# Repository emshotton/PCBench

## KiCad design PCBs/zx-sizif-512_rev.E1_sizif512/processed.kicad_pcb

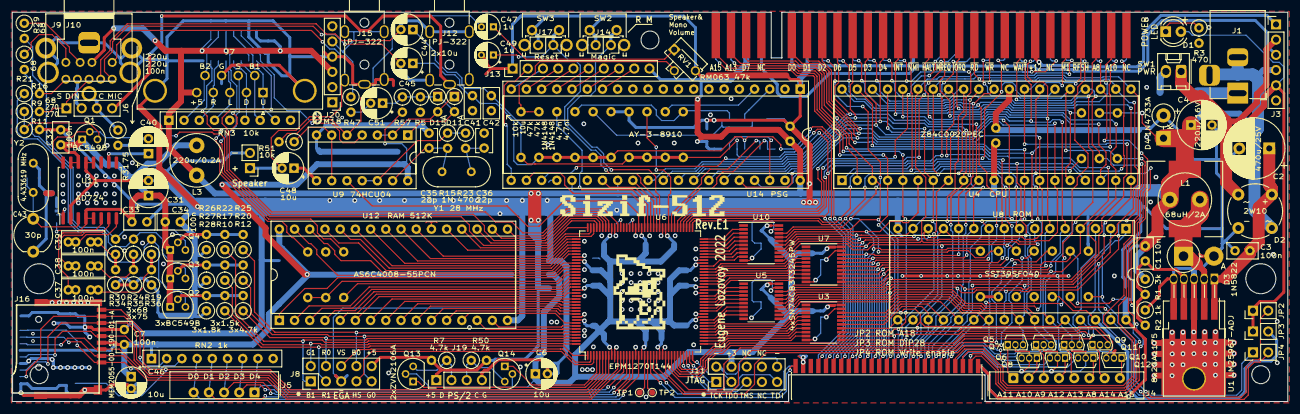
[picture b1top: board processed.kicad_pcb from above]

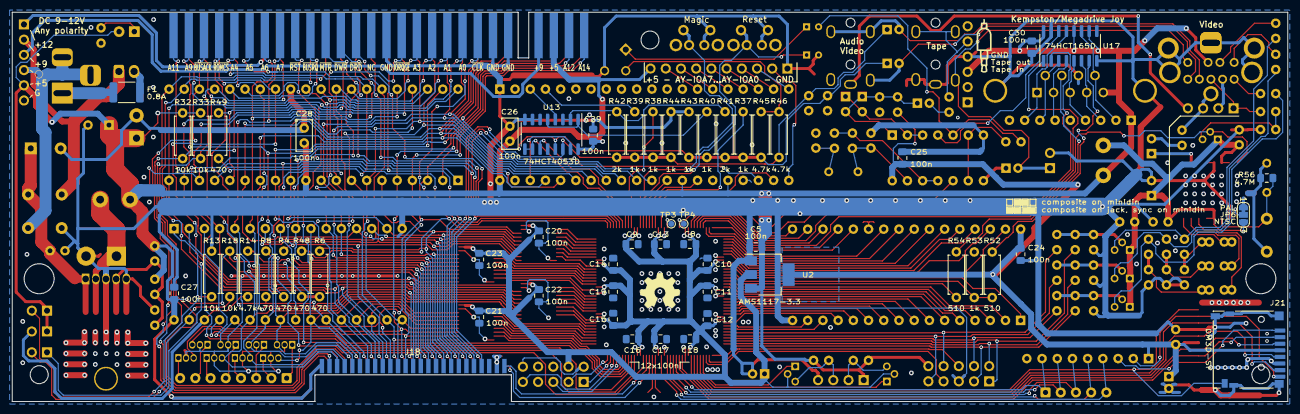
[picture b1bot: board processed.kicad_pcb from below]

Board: 2 copper layers, 213.0 x 65.0 mm, 193 parts (58 on the bottom side), 248 nets.

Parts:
C1: 10n; C_Disc_D5.0mm_W2.5mm_P2.50mm
C2: 470u/25V; CP_Radial_D10.0mm_P5.00mm
C3, C7, C26, C28, C32, C33, C34: 100n; C_Disc_D5.0mm_W2.5mm_P2.50mm
C4: 220u/16V; CP_Radial_D8.0mm_P3.50mm
C5, C8, C9, C10, C11, C12, C13, C14, C15, C16, C17, C18, C19, C20, C21, C22, C23, C24, C27, C29: 100n; C_0805_2012Metric_Pad1.15x1.40mm_HandSolder
C6, C44, C45, C46, C48, C51: 10u; CP_Radial_D5.0mm_P2.00mm
C25, C30: 100n; C_0805_2012Metric_Pad1.18x1.45mm_HandSolder
C31, C40: 220u; CP_Radial_D6.3mm_P2.50mm
C35, C36: 22p; C_Disc_D3.8mm_W2.6mm_P2.50mm
C37, C38, C39: 100n; C_Rect_L7.0mm_W3.5mm_P2.50mm_P5.00mm
C41, C42: 4.7n; C_Disc_D5.0mm_W2.5mm_P2.50mm
C43: 30p; C_Trim_D6.3mm_P5.50mm
C47, C49: 1u; CP_Radial_D4.0mm_P2.00mm
D1: LED; LED_D4.0mm
D2: 2W10; Diode_Bridge_Round_D10.0mm
D3: 1N5822; D_DO-201AD_P5.08mm_Vertical_AnodeUp
D4: 1N4733A; D_DO-15_P3.81mm_Vertical_KathodeUp
D11, D15: 1N4148; D_DO-35_SOD27_P2.54mm_Vertical_AnodeUp
F1: 0.8A; Fuse_1812_4532Metric_Pad1.30x3.40mm_HandSolder
H1, H2: MountingHole; MountingHole_5mm_7mm_fence
H3, H4, H5: MountingHole; MountingHole_3mm
J1: DS-210; BarrelJack_Horizontal
J2: Conn_02x28_Row_Letter_First; ZX_EDGE
J3, J20: Pin header 1x6 Pitch=2.54mm; PinHeader_1x06_P2.54mm_Vertical
J4: DS1020-08; FFC_FPC_1x08
J5: DS1020-05; FFC_FPC_1x05
J6, J19: Pin header 1x4 Pitch=2.54mm; PinHeader_1x04_P2.54mm_Vertical
J7: DB9-M; DSUB-9_Male_Horizontal_P2.77x2.84mm_EdgePinOffset4.94mm_Hou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
J8, J11: Pin header 2x5 Pitch=2.54mm; PinHeader_2x05_P2.54mm_Vertical
J9: Mini-DIN-9; minidin-9
J10: RCJ-014; CUI_RCJ-01X-WIDE
J12, J15: PJ-322
J13: Pin header 1x10 Pitch=2.54mm; PinHeader_1x10_P2.54mm_Vertical
J14, J17: Pin header 1x2 Pitch=2.54mm; PinHeader_2x01_P2.54mm_Vertical
J16: MEM2055-00-190-01-A; GCT-MEM2055-00-190-01-A
J18: Pin socket 3x25 or 2xPin socket 1x25 Pitch=1.27mm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; PinHeader_2x25_P1.27mm_Edge_SMD
J21: DM3D-SF; microSD_HC_Hirose_DM3D-SF
JP2, JP3, JP4: Jumper / Pin header 1x2 Pitch=2.54mm; PinHeader_1x02_P2.54mm_Vertical
JP6: Jumper_3_Bridged12; SolderJumper-3_P1.3mm_Bridged12_RoundedPad1.0x1.5mm_NumberL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
L1: 68uH/2A; L_Radial_D8.7mm_P5.00mm_Fastron_07HCP
L2: 68uH/2A; L_12x12mm_H8mm
L3: 220u/0.2A; L_Radial_D8.7mm_P5.00mm_Fastron_07HCP
LOGO1: graphic; black-mage-12.5x8.6-r
LOGO2: Logo_Open_Hardware_Small; OSHW-Symbol_6.7x6mm_SilkScreen
LOGO3: graphic; jack35
LOGO4: graphic; bluetooth_small
LOGO5: graphic; sizif512
LS1: Pin header 1x2 Pitch=2.54mm; PinHeader_1x02_P2.54mm_Vertical
Q1, Q2, Q3, Q4: BC549B; TO-92
Q5, Q6, Q7, Q8, Q9, Q10, Q11, Q12: 2SA1175; TO-92S
Q13, Q14: ZVN2106A; TO-92
R1: 3k; R_Axial_DIN0207_L6.3mm_D2.5mm_P2.54mm_Vertical
R2: 1k; R_Axial_DIN0207_L6.3mm_D2.5mm_P2.54mm_Vertical
R3, R23: 470; R_Axial_DIN0207_L6.3mm_D2.5mm_P2.54mm_Vertical
R4, R6, R8, R48, R49: 470; R_Axial_DIN0207_L6.3mm_D2.5mm_P7.62mm_Horizontal
R5, R57: 47k; R_Axial_DIN0207_L6.3mm_D2.5mm_P2.54mm_Vertical
R7, R12, R20, R25, R50: 4.7k; R_Axial_DIN0207_L6.3mm_D2.5mm_P2.54mm_Vertical
R9, R11: 270; R_Axial_DIN0207_L6.3mm_D2.5mm_P2.54mm_Vertical
R10, R17, R22: 1.5k; R_Axial_DIN0207_L6.3mm_D2.5mm_P2.54mm_Vertical
R13, R18, R32, R33: 10k; R_Axial_DIN0207_L6.3mm_D2.5mm_P7.62mm_Horizontal
R14, R45, R46: 4.7k; R_Axial_DIN0207_L6.3mm_D2.5mm_P7.62mm_Horizontal
R15: 1M; R_Axial_DIN0207_L6.3mm_D2.5mm_P2.54mm_Vertical
R16, R19, R21, R24, R29, R30: 68; R_Axial_DIN0207_L6.3mm_D2.5mm_P2.54mm_Vertical
R26, R27, R28: 1.8k; R_Axial_DIN0207_L6.3mm_D2.5mm_P2.54mm_Vertical
R31, R34, R35, R36: 75; R_Axial_DIN0207_L6.3mm_D2.5mm_P2.54mm_Vertical
R37, R38, R39, R40, R43, R44, R53: 1k; R_Axial_DIN0207_L6.3mm_D2.5mm_P7.62mm_Horizontal
R41, R42: 2k; R_Axial_DIN0207_L6.3mm_D2.5mm_P7.62mm_Horizontal
R47, R51: 10k; R_Axial_DIN0207_L6.3mm_D2.5mm_P2.54mm_Vertical
R52, R54: 510; R_Axial_DIN0207_L6.3mm_D2.5mm_P7.62mm_Horizontal
R56: 4.7M; R_0805_2012Metric_Pad1.15x1.40mm_HandSolder
RN2: 1k; R_Array_SIP9
RN3: 10k; R_Array_SIP9
RV1: RM063 47k; Potentiometer_Runtron_RM-063_Horizontal
SW1: Jumper / Pin header 1x2 Pitch=2.54mm; Molex_KK-254_AE-6410-02A_1x02_P2.54mm_Vertical
SW2, SW3: Button THT; SW_Tactile_SPST_Angled_PTS645Vx83-2LFS
TP1, TP2, TP3, TP4: TestPoint; TestPoint_Pad_D1.0mm
U1: LM2596T-ADJ; TO-220-263-5_Horizontal_TabDown
U2: AMS1117-3.3; SOT-223-3_TabPin2
U3, U5, U7, U10: SN74CB3T3245PW; TSSOP-20_4.4x6.5mm_P0.65mm
U4: Z84C0020PEC; DIP-40_W15.24mm_Socket
U6: EPM1270T144; LQFP-144_20x20mm_P0.5mm
U8: SST39SF040; DIP-32_W15.24mm_Socket
U9: 74HCU04; DIP-14_W7.62mm_Socket
U11: AD724; SOIC-16W_7.5x10.3mm_P1.27mm
U12: AS6C4008-55PCN; DIP-32_W15.24mm_Socket
U13: 74HCT4053D; SOIC-16_3.9x9.9mm_P1.27mm
U14: AY-3-8910; DIP-40_W15.24mm_Socket
U17: 74HCT165D; SOIC-16_3.9x9.9mm_P1.27mm
Y1: 28 MHz; Crystal_HC49-U_Vertical
Y2: 4.433619 MHz; Crystal_HC49-U_Vertical

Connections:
+3V3: C6.1, C7.2, C8.1, C9.1, C10.1, C11.1, C12.1, C13.1, C14.1, C15.1, C16.1, C17.1, C18.1, C19.1, C20.1, C21.1, C22.1, C23.1, C24.2, C25.2, C46.1, J11.4, J16.4 (VDD), J21.4 (VDD), Q13.2 (G), Q14.2 (G), R57.2, RN2.1 (common), U2.2 (VO), U3.20 (VCC), U5.20 (VCC), U6.9 (VCCIO1), U6.19 (VCCINT), U6.25 (VCCIO1), U6.46 (VCCIO4), U6.56 (VCCINT), U6.64 (VCCIO4), U6.82 (VCCIO3), U6.90 (VCCINT), U6.100 (VCCIO3), U6.116 (VCCIO2), U6.126 (VCCINT), U6.136 (VCCIO2), U7.20 (VCC), U9.14 (VCC), U10.20 (VCC), U12.32 (VCC)
+5V: C1.1, C4.1, C5.2, C26.2, C27.2, C28.2, C29.2, C30.2, D1.2 (A), D4.1 (A1), J2.A3 (Pin_a3), J3.5, J7.5, J8.10, J9.2, J13.10, J18.1, J18.2, J19.1, J20.3, JP2.1, JP3.1, L1.2, L2.2, L3.1, R1.1, R6.2, R7.2, R18.1, R32.2, R33.2, R48.2, R50.2, RN3.1 (common), U2.3 (VI), U4.11 (VCC), U8.32 (VCC), U13.16 (VDD), U14.25 (A8), U14.28 (BC2), U14.40 (VCC), U17.10 (DS), U17.12 (D1), U17.16 (VCC)
+5VA: C31.1, C32.2, C33.2, C34.2, JP6.3 (B), L3.2, Q1.1 (C), Q2.1 (C), Q3.1 (C), Q4.1 (C), U11.4 (AVCC), U11.5 (ENCD), U11.14 (DVCC), U11.15 (VSYNC)
+9V: J2.A4 (Pin_a4), J3.3
+12V: J2.B22 (Pin_b22), J3.1
/A0: J2.A9 (Pin_a9), J18.35, U4.30 (A0), U7.18 (B0), U8.12 (A0)
/A1: J2.A10 (Pin_a10), J18.33, U4.31 (A1), U7.17 (B1), U8.11 (A1)
/A2: J2.A11 (Pin_a11), J18.32, U4.32 (A2), U7.16 (B2), U8.10 (A2)
/A3: J2.A12 (Pin_a12), J18.31, U4.33 (A3), U7.15 (B3), U8.9 (A3)
/A4: J2.A24 (Pin_a24), J18.30, U4.34 (A4), U7.14 (B4), U8.8 (A4)
/A5: J2.A23 (Pin_a23), J18.36, U4.35 (A5), U8.7 (A5), U10.12 (B6)
/A6: J2.A22 (Pin_a22), J18.29, U4.36 (A6), U7.13 (B5), U8.6 (A6)
/A7: J2.A21 (Pin_a21), J18.28, U4.37 (A7), U7.12 (B6), U8.5 (A7)
/A8: J2.B26 (Pin_b26), J18.6, Q10.3 (B), U4.38 (A8), U5.13 (B5), U8.27 (A8)
/A9: J2.A27 (Pin_a27), J18.9, Q7.3 (B), U4.39 (A9), U5.12 (B6), U8.26 (A9)
/A10: J2.B27 (Pin_b27), J18.11, Q6.3 (B), U3.18 (B0), U4.40 (A10), U8.23 (A10)
/A11: J2.A28 (Pin_a28), J18.10, Q5.3 (B), U4.1 (A11), U5.11 (B7), U8.25 (A11)
/A12: J2.A2 (Pin_a2), J18.8, Q8.3 (B), U4.2 (A12), U7.11 (B7), U8.4 (A12)
/A13: J2.B2 (Pin_b2), J18.20, Q9.3 (B), U4.3 (A13), U8.28 (A13), U10.17 (B1)
/A14: J2.A1 (Pin_a1), J18.24, Q11.3 (B), U3.12 (B6), U4.4 (A14)
/A15: J2.B1 (Pin_b1), J18.23, Q12.3 (B), U3.13 (B5), U4.5 (A15)
/AY_ABC: U6.79 (IO3_79), U13.9 (C), U13.10 (B)
/AY_BC1: U6.86 (IO3_86), U14.29 (BC1)
/AY_BDIR: U6.87 (IO3_87), U14.27 (BDIR)
/AY_CLK: U6.89 (IO3_89/GCLK2), U14.22 (CLOCK)
/AY_MONO: U6.80 (IO3_80), U13.11 (A)
/BUS0: J18.49, U6.22 (IO1_22)
/BUS1: J18.50, U6.23 (IO1_23)
/Blue0: J8.8, R25.1, U6.140 (IO2_140)
/Blue1: J8.1, R22.1, U6.143 (IO2_143)
/CLK28: U6.91 (IO3_91/GCLK3), U9.10
/CLKCPU: J18.34, R6.1, U4.6 (~CLK), U10.16 (B2)
/Csync: Q1.2 (B), U6.105 (IO3_105), U11.16 (HSYNC)
/D0: J2.B6 (Pin_b6), J18.37, U4.14 (D0), U8.13 (D0), U10.13 (B5), U14.37 (DA0)
/D1: J2.B7 (Pin_b7), J18.38, U4.15 (D1), U8.14 (D1), U10.14 (B4), U14.36 (DA1)
/D2: J2.B8 (Pin_b8), J18.39, U4.12 (D2), U8.15 (D2), U10.15 (B3), U14.35 (DA2)
/D3: J2.B11 (Pin_b11), J18.22, U3.14 (B4), U4.8 (D3), U8.17 (D3), U14.34 (DA3)
/D4: J2.B12 (Pin_b12), J18.21, U3.11 (B7), U4.7 (D4), U8.18 (D4), U14.33 (DA4)
/D5: J2.B10 (Pin_b10), J18.18, U3.15 (B3), U4.9 (D5), U8.19 (D5), U14.32 (DA5)
/D6: J2.B9 (Pin_b9), J18.16, U3.16 (B2), U4.10 (D6), U8.20 (D6), U14.31 (DA6)
/D7: J2.B3 (Pin_b3), J18.14, U3.17 (B1), U4.13 (D7), U8.21 (D7), U14.30 (DA7)
/Green0: J8.9, R20.1, U6.141 (IO2_141)
/Green1: J8.2, R17.1, U6.144 (IO2_144)
/Hsync: J8.7, U6.3 (IO1_3)
/JOY_SEL: R54.1, U6.121 (IO2_121)
/JOY_SEL0: J7.7, R54.2
/KD0: J5.5, RN2.4 (R3), U6.18 (IO1_18/GCLK0)
/KD1: J5.4, RN2.5 (R4), U6.16 (IO1_16)
/KD2: J5.3, RN2.6 (R5), U6.15 (IO1_15)
/KD3: J5.2, RN2.7 (R6), U6.14 (IO1_14)
/KD4: J5.1, RN2.8 (R7), U6.13 (IO1_13)
/MIX_L: C42.2, C44.1, J18.43, R38.1, R39.1, R42.1, R44.1, R46.1, U13.14 (X)
/MIX_R: C41.2, C45.1, J18.42, R37.1, R40.1, R41.1, R43.1, R45.1, U13.13 (X1)
/PS2_CLK: Q14.1 (S), U6.4 (IO1_4)
/PS2_DAT: Q13.1 (S), U6.5 (IO1_5)
/RA14: U6.30 (IO1_30), U8.29 (A14)
/RA15: U6.29 (IO1_29), U8.3 (A15)
/RA16: U6.28 (IO1_28), U8.2 (A16)
/RA17: R14.1, U6.27 (IO1_27)
/Red0: J8.4, R12.1, U6.142 (IO2_142)
/Red1: J8.3, R10.1, U6.1 (IO1_1)
/SD_CD: J16.9 (DET_B), J21.9 (DET_B), U6.6 (IO1_6)
/SD_CS: J16.2 (DAT3/CD), J21.2 (DAT3/CD), U6.12 (IO1_12)
/SD_DAT1: J16.8 (DAT1), J21.8 (DAT1), RN2.2 (R1)
/SD_DAT2: J16.1 (DAT2), J21.1 (DAT2), RN2.3 (R2)
/SD_MISO: J16.7 (DAT0), J21.7 (DAT0), U6.7 (IO1_7)
/SD_MOSI: J16.3 (CMD), J21.3 (CMD), U6.11 (IO1_11)
/SD_SCK: J16.5 (CLK), J21.5 (CLK), U6.8 (IO1_8)
/SHIFT_CLK: U6.98 (IO3_98), U17.2 (CP)
/SHIFT_OUT: R52.2, R53.2, U6.120 (IO2_120)
/SHIFT_PL: U6.103 (IO3_103), U17.1 (~PL)
/SND_DAC_L: R38.2, U6.81 (IO3_81)
/SND_DAC_R: R37.2, U6.88 (IO3_88)
/SND_L: C44.2, J9.8, J12.T
/SND_MONO: C48.2, J9.6, J15.R1, LS1.1
/SND_R: C45.2, J9.9, J12.R1
/TAPE_IN: J15.T, J20.5, R47.1
/TAPE_IN0: U9.4, U17.14 (D3)
/TCK: J11.1, U6.35 (TCK)
/TDI: J11.9, U6.34 (TDI)
/TDO: J11.3, U6.36 (TDO)
/TMS: J11.5, U6.33 (TMS)
/VA0: U6.134 (IO2_134), U12.12 (A0)
/VA1: U6.133 (IO2_133), U12.11 (A1)
/VA2: U6.132 (IO2_132), U12.10 (A2)
/VA3: U6.131 (IO2_131), U12.9 (A3)
/VA4: U6.130 (IO2_130), U12.8 (A4)
/VA5: U6.129 (IO2_129), U12.7 (A5)
/VA6: U6.127 (IO2_127), U12.6 (A6)
/VA7: U6.125 (IO2_125), U12.5 (A7)
/VA8: U6.112 (IO2_112), U12.27 (A8)
/VA9: U6.111 (IO2_111), U12.26 (A9)
/VA10: U6.106 (IO3_106), U12.23 (A10)
/VA11: U6.110 (IO2_110), U12.25 (A11)
/VA12: U6.124 (IO2_124), U12.4 (A12)
/VA13: U6.113 (IO2_113), U12.28 (A13)
/VA14: U6.123 (IO2_123), U12.3 (A14)
/VA15: U6.118 (IO2_118), U12.31 (A15)
/VA16: U6.122 (IO2_122), U12.2 (A16)
/VA17: U6.119 (IO2_119), U12.1 (A18)
/VA18: U6.117 (IO2_117), U12.30 (A17)
/VD0: U6.137 (IO2_137), U12.13 (D0)
/VD1: U6.139 (IO2_139), U12.14 (D1)
/VD2: U6.138 (IO2_138), U12.15 (D2)
/VD3: U6.101 (IO3_101), U12.17 (D3)
/VD4: U6.102 (IO3_102), U12.18 (D4)
/VD5: U6.104 (IO3_104), U12.19 (D5)
/VD6: U6.108 (IO3_108), U12.20 (D6)
/VD7: U6.107 (IO3_107), U12.21 (D7)
/VID_B: J9.1, R29.1
/VID_COMP: J6.3, J10.1 (In), R31.1
/VID_DIN: J6.2, J9.4
/VID_G: J9.3, R21.1
/VID_MIC: J6.4, J12.S
/VID_R: J9.7, R16.2
/VID_SYNC: J6.1, J9.5, R9.2
/Vsync: J8.6, U6.2 (IO1_2)
/xA0: U6.62 (IO4_62), U7.2 (A0)
/xA1: U6.61 (IO4_61/DEV_CLRn), U7.3 (A1)
/xA2: U6.60 (IO4_60/DEV_OE), U7.4 (A2)
/xA3: U6.59 (IO4_59), U7.5 (A3)
/xA4: U6.58 (IO4_58), U7.6 (A4)
/xA5: U6.66 (IO4_66), U10.8 (A6)
/xA6: U6.57 (IO4_57), U7.7 (A5)
/xA7: U6.55 (IO4_55), U7.8 (A6)
/xA8: U5.7 (A5), U6.45 (IO4_45)
/xA9: U5.8 (A6), U6.44 (IO4_44)
/xA10: U3.2 (A0), U6.42 (IO4_42)
/xA11: U5.9 (A7), U6.43 (IO4_43)
/xA12: U6.53 (IO4_53), U7.9 (A7)
/xA13: U6.71 (IO4_71), U10.3 (A1)
/xA14: U3.8 (A6), U6.32 (IO1_32)
/xA15: U3.7 (A5), U6.37 (IO4_37)
/xCLKCPU: U6.70 (IO4_70), U10.4 (A2)
/xD0: U6.67 (IO4_67), U10.7 (A5)
/xD1: U6.68 (IO4_68), U10.6 (A4)
/xD2: U6.69 (IO4_69), U10.5 (A3)
/xD3: U3.6 (A4), U6.38 (IO4_38)
/xD4: U3.9 (A7), U6.31 (IO1_31)
/xD5: U3.5 (A3), U6.39 (IO4_39)
/xD6: U3.4 (A2), U6.40 (IO4_40)
/xD7: U3.3 (A1), U6.41 (IO4_41)
/~BUSACK: J2.A26 (Pin_a26), J18.3, U4.23 (~BUSACK)
/~BUSRQ: J2.A19 (Pin_a19), J18.5, R32.1, U4.25 (~BUSRQ)
/~CLKCPU: J2.A8 (Pin_a8), R48.1, U10.18 (B0)
/~DRD: J2.A16 (Pin_a16), U6.78 (IO3_78)
/~DWR: J2.A17 (Pin_a17), U6.77 (IO3_77)
/~HALT: J2.B15 (Pin_b15), J18.4, U4.18 (~HALT)
/~INTB: J2.B13 (Pin_b13), R49.1, U4.16 (~INT)
/~INT: J18.40, R49.2, U6.73 (IO3_73)
/~IORQGE: J2.A13 (Pin_a13), J18.19, R4.1, U10.11 (B7)
/~IORQ: J2.B17 (Pin_b17), J18.13, R4.2, U4.20 (~IORQ)
/~JOY_B1: J7.6, RN3.7 (R6), U17.3 (D4)
/~JOY_B2: J7.9, RN3.2 (R1), U17.11 (D0)
/~JOY_DOWN: J7.2, RN3.6 (R5), U17.4 (D5)
/~JOY_LEFT: J7.3, RN3.4 (R3), U17.5 (D6)
/~JOY_RIGHT: J7.4, RN3.3 (R2), U17.6 (D7)
/~JOY_UP: J7.1, RN3.8 (R7), U17.13 (D2)
/~M1: J2.B24 (Pin_b24), J18.25, U4.27 (~M1), U5.14 (B4)
/~MAGIC: J14.1, SW2.2, U6.84 (IO3_84)
/~MREQ: J2.B16 (Pin_b16), J18.27, U4.19 (~MREQ), U5.18 (B0)
/~MTR: J2.A18 (Pin_a18), U6.76 (IO3_76)
/~NMI: J2.B14 (Pin_b14), J18.41, U4.17 (~NMI), U6.74 (IO3_74)
/~RD: J2.B18 (Pin_b18), J18.17, U4.21 (~RD), U5.15 (B3), U8.24 (~OE)
/~RFSH: J2.B25 (Pin_b25), J18.26, U4.28 (~RFSH), U5.17 (B1)
/~ROMCSB: J2.A25 (Pin_a25), J18.12, R8.2, U8.22 (~CE)
/~ROMCS: R8.1, U6.24 (IO1_24)
/~RSTCPU: J2.A20 (Pin_a20), J18.44, U4.26 (~RESET), U6.75 (IO3_75), U14.23 (~RESET)
/~RST: C49.1, J17.1, SW3.2, U6.85 (IO3_85)
/~VRD: U6.109 (IO2_109), U12.24 (~OE)
/~VWR: U6.114 (IO2_114), U12.29 (~WE)
/~WAIT: J2.B21 (Pin_b21), J18.7, R33.1, U4.24 (~WAIT)
/~WR: J2.B19 (Pin_b19), J18.15, JP4.1, U4.22 (~WR), U5.16 (B2)
/~xCLKCPU: U6.72 (IO4_72), U10.2 (A0)
/~xIORQGE: U6.63 (IO4_63), U10.9 (A7)
/~xM1: U5.6 (A4), U6.48 (IO4_48)
/~xMREQ: U5.2 (A0), U6.52 (IO4_52)
/~xRD: U5.5 (A3), U6.49 (IO4_49)
/~xRFSH: U5.3 (A1), U6.51 (IO4_51)
/~xWR: U5.4 (A2), U6.50 (IO4_50)
GND: C2.2, C3.2, C4.2, C5.1, C6.2, C7.1, C8.2, C9.2, C10.2, C11.2, C12.2, C13.2, C14.2, C15.2, C16.2, C17.2, C18.2, C19.2, C20.2, C21.2, C22.2, C23.2, C24.1, C25.1, C26.1, C27.1, C28.1, C29.1, C30.1, C31.2, C32.1, C33.1, C34.1, C35.1, C36.1, C41.1, C42.1, C43.2, C46.2, C49.2, D2.1 (-), D3.2 (A), D4.2 (A2), J2.A6 (Pin_a6), J2.A7 (Pin_a7), J2.A14 (Pin_a14), J3.6, J7.0 (PAD), J7.8, J8.5, J9.0, J10.2 (Ext), J11.2, J11.10, J12.R2, J13.1, J14.2, J15.R2, J15.S, J16.6 (VSS), J16.10 (DET_A), J16.11 (SHIELD), J17.2, J18.47, J18.48, J19.4, J20.4, J21.6 (VSS), J21.10 (DET_A), J21.11 (SHIELD), JP6.1 (A), LS1.2, Q5.2 (C), Q6.2 (C), Q7.2 (C), Q8.2 (C), Q9.2 (C), Q10.2 (C), Q11.2 (C), Q12.2 (C), R2.1, R3.2, R5.2, R11.2, R13.1, R26.1, R27.1, R28.1, R34.1, R35.1, R36.1, R43.2, R44.2, R53.1, R56.1, RV1.3, SW2.1, SW3.1, U1.3 (GND), U1.5 (~ON/OFF), U2.1 (GND), U3.10 (GND), U3.19 (~OE), U4.29 (GND), U5.10 (GND), U5.19 (~OE), U6.10 (GNDIO), U6.17 (GNDINT), U6.26 (GNDIO), U6.47 (GNDIO), U6.54 (GNDINT), U6.65 (GNDIO), U6.83 (GNDIO), U6.92 (GNDINT), U6.99 (GNDIO), U6.115 (GNDIO), U6.128 (GNDINT), U6.135 (GNDIO), U7.10 (GND), U7.19 (~OE), U8.16 (GND), U9.7 (GND), U10.10 (GND), U10.19 (~OE), U11.2 (AGND), U11.12 (SELECT), U11.13 (DGND), U12.16 (GND), U12.22 (~CE), U13.6 (INH), U13.7 (VEE), U13.8 (VSS), U14.1 (VSS), U14.24 (~A9), U17.8 (GND), U17.15 (~CE), Y2.2
unnamed: C1.2, R1.2, R2.2, U1.4 (FB)
unnamed: C2.1, C3.1, D2.3 (+), U1.1 (VIN)
unnamed: C35.2, R15.2, U9.13, Y1.2
unnamed: C36.2, R23.2, Y1.1
unnamed: C37.1, R19.1, R36.2
unnamed: C37.2, U11.6 (RIN)
unnamed: C38.1, R24.1, R35.2
unnamed: C38.2, U11.7 (GIN)
unnamed: C39.1, R30.1, R34.2
unnamed: C39.2, U11.8 (BIN)
unnamed: C40.1, U11.10 (COMP)
unnamed: C40.2, R31.2
unnamed: C43.1, R56.2, U11.3 (FIN), Y2.1
unnamed: C47.1, RV1.1
unnamed: C47.2, R51.2, U9.5
unnamed: C48.1, U9.8
unnamed: C51.1, D11.2 (A), D15.1 (K), R5.1, R57.1, U9.1
unnamed: C51.2, R47.2
unnamed: D1.1 (K), R3.1
unnamed: D2.2, J1.2, J1.3, J3.4
unnamed: D2.4, J3.2, SW1.1 (A)
unnamed: D3.1 (K), L1.1, L2.1, U1.2 (OUT)
unnamed: D11.1 (K), D15.2 (A), U9.2, U9.3
unnamed: F1.1, J1.1
unnamed: F1.2, SW1.2 (B)
unnamed: J4.1, Q5.1 (E)
unnamed: J4.2, Q6.1 (E)
unnamed: J4.3, Q7.1 (E)
unnamed: J4.4, Q8.1 (E)
unnamed: J4.5, Q9.1 (E)
unnamed: J4.6, Q10.1 (E)
unnamed: J4.7, Q11.1 (E)
unnamed: J4.8, Q12.1 (E)
unnamed: J13.2, U14.21 (IOA0)
unnamed: J13.3, U14.20 (IOA1)
unnamed: J13.4, U14.19 (IOA2)
unnamed: J13.5, U14.18 (IOA3)
unnamed: J13.6, U14.17 (IOA4)
unnamed: J13.7, U14.16 (IOA5)
unnamed: J13.8, U14.15 (IOA6)
unnamed: J13.9, U14.14 (IOA7)
unnamed: J19.2, Q13.3 (D), R7.1
unnamed: J19.3, Q14.3 (D), R50.1
unnamed: JP2.2, R13.2, U8.1 (A18)
unnamed: JP3.2, R14.2, U8.30 (A17)
unnamed: JP4.2, R18.2, U8.31 (~WE)
unnamed: JP6.2 (C), U11.1 (STDN)
unnamed: Q1.3 (E), R9.1, R11.1
unnamed: Q2.2 (B), R10.2, R12.2, R28.2
unnamed: Q2.3 (E), R16.1, R19.2
unnamed: Q3.2 (B), R17.2, R20.2, R27.2
unnamed: Q3.3 (E), R21.2, R24.2
unnamed: Q4.2 (B), R22.2, R25.2, R26.2
unnamed: Q4.3 (E), R29.2, R30.2
unnamed: R15.1, R23.1, U9.11, U9.12
unnamed: R39.2, U14.4 (A)
unnamed: R40.2, U13.1 (Y1), U13.5 (Z0)
unnamed: R41.2, R42.2, U13.2 (Y0), U13.3 (Z1)
unnamed: R45.2, R46.2, RV1.2
unnamed: R51.1, U9.6, U9.9
unnamed: R52.1, U17.7 (~Q7)
unnamed: TP1.1, U6.20 (IO1_20/GCLK1)
unnamed: TP2.1, U6.21 (IO1_21)
unnamed: TP3.1, U6.93 (IO3_93)
unnamed: TP4.1, U6.97 (IO3_97)
unnamed: U13.4 (Z), U14.3 (B)
unnamed: U13.15 (Y), U14.38 (C)
